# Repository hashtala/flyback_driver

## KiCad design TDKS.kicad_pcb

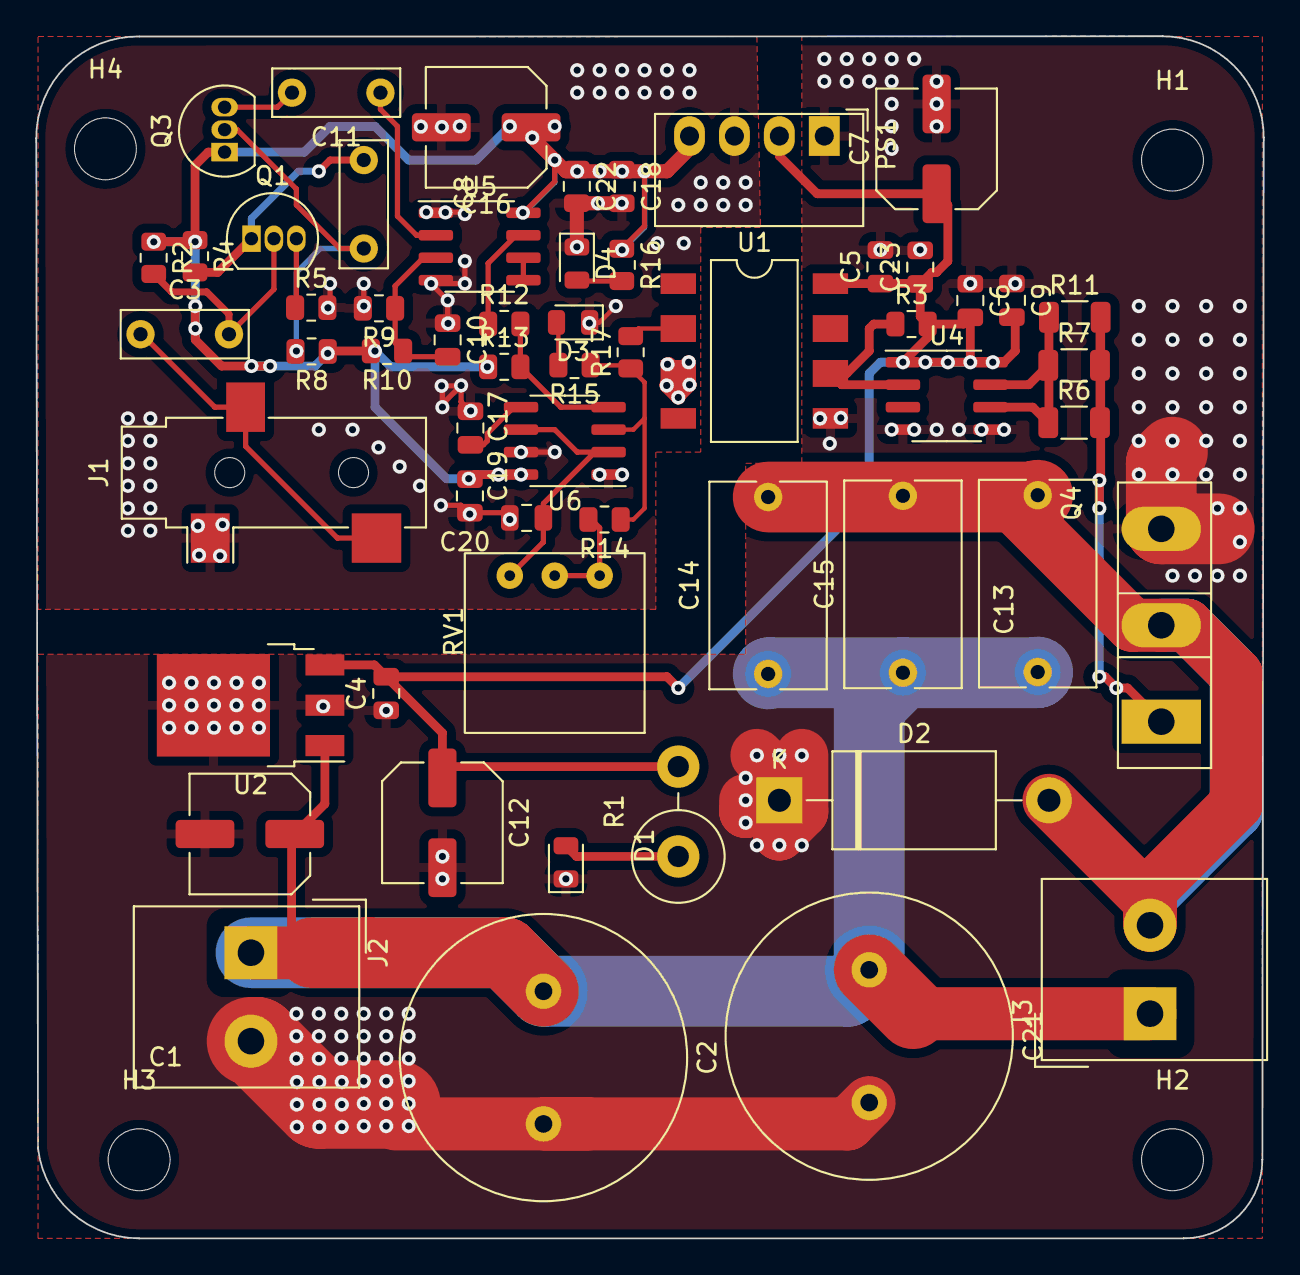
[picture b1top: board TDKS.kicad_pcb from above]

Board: 2 copper layers, 69.4 x 68.0 mm, 61 parts (0 on the bottom side), 28 nets.

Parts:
C1: 0.22uF; C_Elec_6.3x5.4
C2, C21: 470uF; C_Radial_D16.0mm_H25.0mm_P7.50mm
C3, C8, C11: C; C_Rect_L7.0mm_W2.5mm_P5.00mm
C4, C5, C6, C9, C10, C17, C18, C22, C23: 100nF; C_0805_2012Metric
C7: 0.1uF; C_Elec_6.3x5.4
C12: 2.2uF; C_Elec_6.3x5.4
C13, C14, C15: C; C_Rect_L11.5mm_W6.4mm_P10.00mm_MKT
C16: 10uF; C_Elec_6.3x5.4
C19: 1uF; C_0805_2012Metric
C20: 4.7nF; C_0805_2012Metric
D1: PWR12; LED_0805_2012Metric
D2: DIODE; D_DO-201AE_P15.24mm_Horizontal
D3: RED; LED_0805_2012Metric
D4: LED; LED_0805_2012Metric
H1, H2, H3, H4: MH; MountingHole_3.5mm
J1: AudioJack3; Jack_3.5mm_CUI_SJ-3523-SMT_Horizontal
J2: PWR; Altech_AK300_1x02_P5.00mm_45-Degree
J3: TDKS Winding; Altech_AK300_1x02_P5.00mm_45-Degree
PS1: MEE1S1205SC; Converter_DCDC_Murata_MEE1SxxxxSC_THT
Q1, Q3: NPN; TO-92L_Inline
Q4: IRFP250; TO-247-3_Vertical
R1: 3.3k; R_Axial_DIN0516_L15.5mm_D5.0mm_P5.08mm_Vertical
R2: 330k; R_0805_2012Metric
R3, R4, R14: 4.7k; R_0805_2012Metric
R5, R15, R16: 1k; R_0805_2012Metric
R6, R7, R11: 10; R_1206_3216Metric
R8: 1M; R_0805_2012Metric
R9: 100; R_0805_2012Metric
R10: 4700; R_0805_2012Metric
R12, R13: 0; R_0805_2012Metric
R17: 330; R_0805_2012Metric
RV1: 10K; LABIS_10K_TRIM
U1: 6N135; PowerIntegrations_SMD-8
U2: L7812; TO-252-3_TabPin2
U4: MIC4421; SOIC-8_3.9x4.9mm_P1.27mm
U5: LM311; SOIC-8_3.9x4.9mm_P1.27mm
U6: NE555D; SOIC-8_3.9x4.9mm_P1.27mm

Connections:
+5V: C16.1, C18.1, C19.1, C22.1, PS1.4 (+Vout), Q3.1 (C), R2.1, R4.1, R8.1, R10.2, R13.1, R16.1, U5.8 (V+), U6.8 (VCC)
+12C: C4.2, C5.1, C6.2, C7.1, C9.2, C12.1, C23.1, PS1.2 (+Vin), R1.2, R3.2, U1.8, U2.3 (OUT), U4.1 (Vs), U4.8 (Vs)
+24V: C1.1, C2.1, C13.1, C14.1, C15.1, C21.1, J2.1, J3.1, U2.1 (IN)
GND: C1.2, C2.2, C4.1, C5.2, C6.1, C7.2, C9.1, C12.2, C21.2, C23.2, D1.1 (K), D2.1 (A), J2.2, PS1.1 (-Vin), Q4.3 (S), U1.5, U2.2 (GND), U4.4 (GND), U4.5 (GND)
GND2: C10.1, C16.2, C17.1, C18.2, C19.2, C20.2, C22.2, D3.1 (K), D4.1 (K), J1.S, PS1.3 (-Vout), R5.2, R9.2, U1.3, U5.1 (GND), U5.4 (V-), U6.1 (GND), U6.7 (DIS)
Modulated_Square: R17.2, U1.2
unnamed: C3.1, J1.R, J1.T
unnamed: C3.2, Q1.2 (B), R2.2
unnamed: C8.1, Q1.1 (C), R4.2
unnamed: C8.2, Q3.2 (B), R8.2
unnamed: C10.2, R9.1, R10.1, U5.3 (-)
unnamed: C11.1, U5.2 (+)
unnamed: C11.2, Q3.3 (E)
unnamed: C13.2, C14.2, C15.2, D2.2 (K), J3.2, Q4.2 (D)
unnamed: C17.2, U6.5 (CV)
unnamed: C20.1, RV1.3, U6.2 (TR), U6.6 (THR)
unnamed: D1.2 (A), R1.1
unnamed: D3.2 (A), R15.2
unnamed: D4.2 (A), R16.2
unnamed: Q1.3 (E), R5.1
unnamed: Q4.1 (G), R6.2, R7.2, R11.2
unnamed: R3.1, U1.6, U4.2 (~In)
unnamed: R6.1, R7.1, R11.1, U4.6 (Out), U4.7 (Out)
unnamed: R12.1, U5.7
unnamed: R12.2, R13.2, U6.4 (R)
unnamed: R14.1, R15.1, R17.1, U6.3 (Q)
unnamed: R14.2, RV1.1, RV1.2
unnamed: U5.5 (BAL), U5.6 (STRB)
